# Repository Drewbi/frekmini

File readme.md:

# FrekMini
A mini version of the [IKEA Frekvens lamp pixel cube](https://www.ikea.com/es/en/new/frekvens-limited-collection-pubcd6f39e0/)

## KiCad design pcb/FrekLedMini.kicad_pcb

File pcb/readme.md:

# FrekMini PCB Design Files
This includes the board files for KiCad as well as the exported Gerber and drill files.

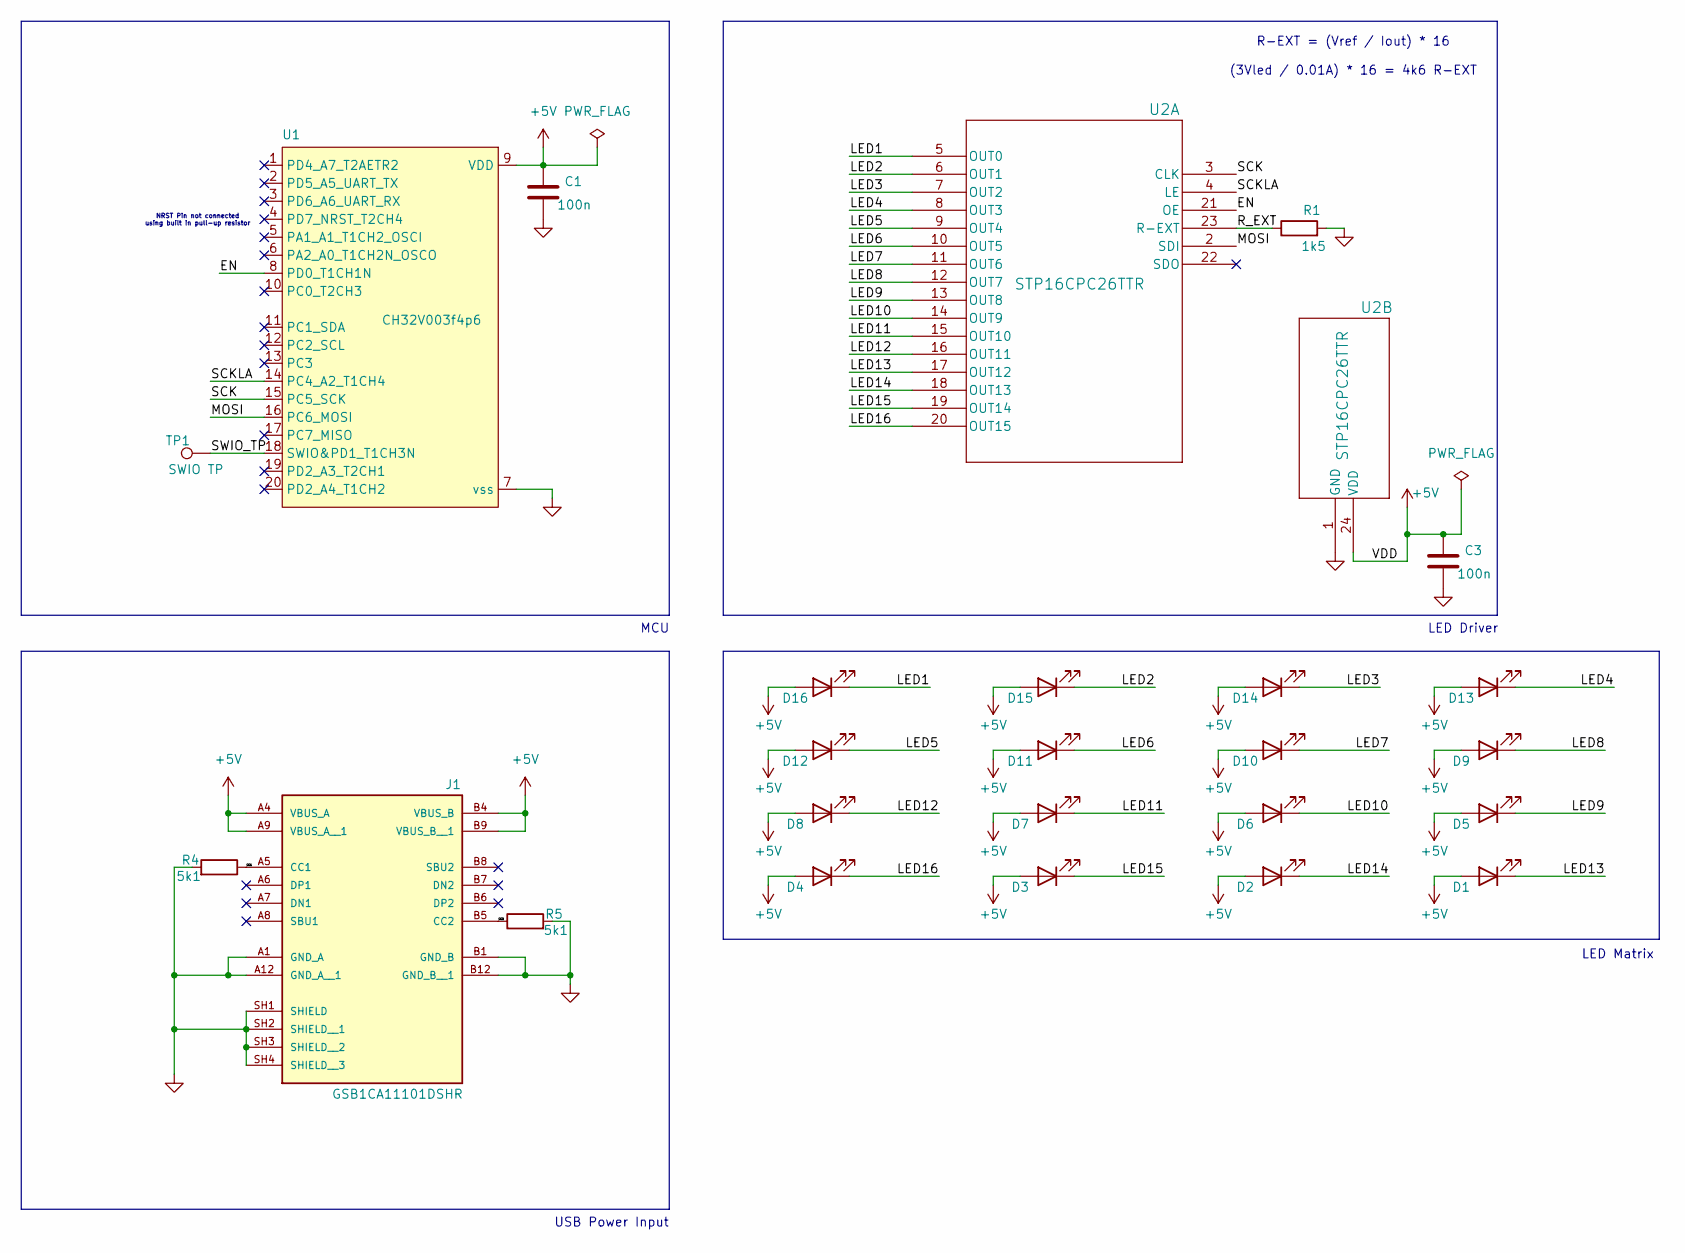
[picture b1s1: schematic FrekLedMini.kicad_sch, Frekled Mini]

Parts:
C1, C3: 100n; C_0402_1005Metric
D1, D2, D3, D4, D5, D6, D7, D8, D9, D10, D11, D12, D13, D14, D15, D16: 2.85v; LED_0402_1005Metric
J1: GSB1CA11101DSHR; AMPHENOL_GSB1CA11101DSHR; PARTREV AX1
R1: 1k5; R_0402_1005Metric
R4, R5: 5k1; R_0402_1005Metric
TP1: SWIO TP; TestPoint_Pad_1.0x1.0mm
U1: CH32V003f4p6; TSSOP-20_4.4x6.5mm_P0.65mm
U2: STP16CPC26TTR; TSSOP_PC26TTR_STM

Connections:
+5V: C1.1, C3.1, D1.2 (A), D2.2 (A), D3.2 (A), D4.2 (A), D5.2 (A), D6.2 (A), D7.2 (A), D8.2 (A), D9.2 (A), D10.2 (A), D11.2 (A), D12.2 (A), D13.2 (A), D14.2 (A), D15.2 (A), D16.2 (A), J1.A4 (VBUS_A), J1.A9 (VBUS_A__1), J1.B4 (VBUS_B), J1.B9 (VBUS_B__1), U1.9 (VDD), U2.24 (VDD)
/CC1: J1.A5 (CC1), R4.1
/CC2: J1.B5 (CC2), R5.1
/EN: U1.8 (PD0_T1CH1N), U2.21 (OE)
/LED1: D16.1 (K), U2.5 (OUT0)
/LED2: D15.1 (K), U2.6 (OUT1)
/LED3: D14.1 (K), U2.7 (OUT2)
/LED4: D13.1 (K), U2.8 (OUT3)
/LED5: D12.1 (K), U2.9 (OUT4)
/LED6: D11.1 (K), U2.10 (OUT5)
/LED7: D10.1 (K), U2.11 (OUT6)
/LED8: D9.1 (K), U2.12 (OUT7)
/LED9: D5.1 (K), U2.13 (OUT8)
/LED10: D6.1 (K), U2.14 (OUT9)
/LED11: D7.1 (K), U2.15 (OUT10)
/LED12: D8.1 (K), U2.16 (OUT11)
/LED13: D1.1 (K), U2.17 (OUT12)
/LED14: D2.1 (K), U2.18 (OUT13)
/LED15: D3.1 (K), U2.19 (OUT14)
/LED16: D4.1 (K), U2.20 (OUT15)
/MOSI: U1.16 (PC6_MOSI), U2.2 (SDI)
/R_EXT: R1.1, U2.23 (R-EXT)
/SCK: U1.15 (PC5_SCK), U2.3 (CLK)
/SCKLA: U1.14 (PC4_A2_T1CH4), U2.4 (LE)
/SWIO_TP: TP1.1, U1.18 (SWIO&PD1_T1CH3N)
GND: C1.2, C3.2, J1.A1 (GND_A), J1.A12 (GND_A__1), J1.B1 (GND_B), J1.B12 (GND_B__1), J1.SH1 (SHIELD), J1.SH2 (SHIELD__1), J1.SH3 (SHIELD__2), J1.SH4 (SHIELD__3), R1.2, R4.2, R5.2, U1.7 (vss), U2.1 (GND)

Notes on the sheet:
MCU
LED Driver
LED Matrix
R-EXT = (Vref / Iout) * 16 (3Vled / 0.01A) * 16 = 4k6 R-EXT
USB Power Input
NRST Pin not connected using built in pull-up resistor

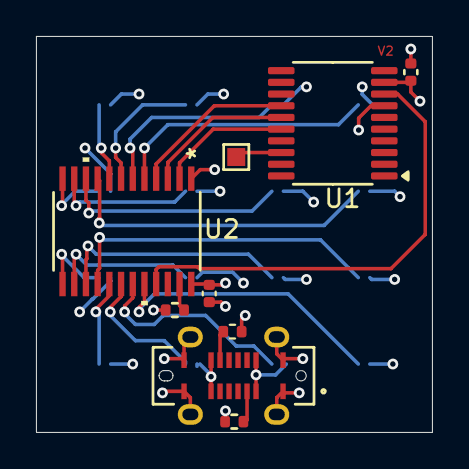
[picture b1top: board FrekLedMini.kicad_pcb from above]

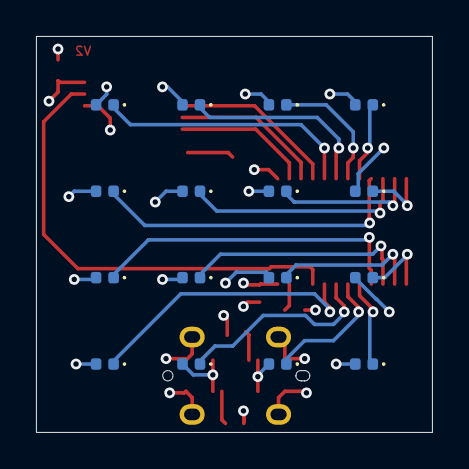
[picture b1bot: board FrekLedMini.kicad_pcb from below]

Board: 4 copper layers, 22.0 x 22.0 mm, 25 parts (16 on the bottom side), 26 nets.

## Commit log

2025-09-11 Initial code
2025-09-13 update project structure and include PCB and 3D models
2025-09-13 update file paths for mrs project
2025-09-13 update artifact name
2025-09-13 add base slides
2025-09-13 update run condition for spell check
2025-09-13 fix out dir path
2025-09-17 add some randomisation
2025-09-17 add random state
2025-09-17 add intro slides
2025-09-17 add content
2025-09-17 remove git lfs
2025-09-17 upload
2025-09-18 add process images and more slides
2025-09-19 add assets
2025-09-19 finish content
2025-09-19 remove border
2025-09-20 add sponsor file
